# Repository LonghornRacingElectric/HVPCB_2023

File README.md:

# 2023 HVPCB

### HVPCB Board

#### 2023 Longhorn Racing Electric

UPDATED: 12/12/2022 - Robert Kirk

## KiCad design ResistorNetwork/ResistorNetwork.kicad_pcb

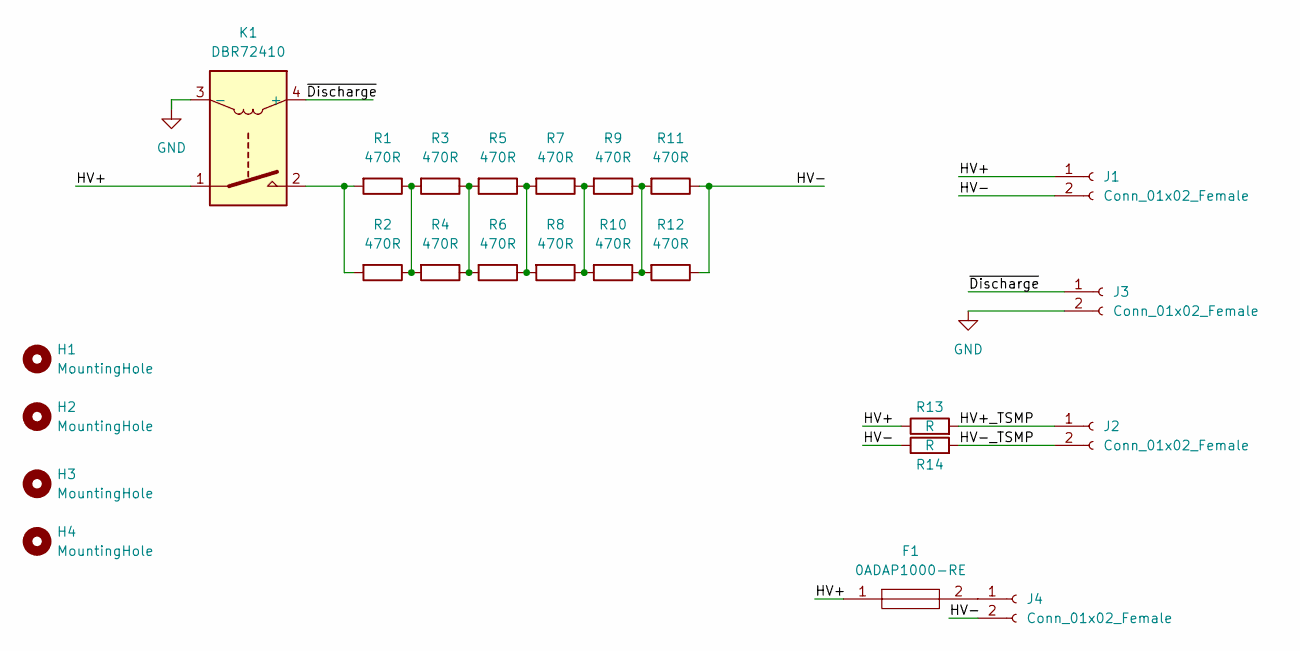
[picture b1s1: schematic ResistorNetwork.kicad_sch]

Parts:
F1: 0ADAP1000-RE; 0ADAP1000RE; Manufacturer_Part_Number 0ADAP1000-RE; Mouser Part Number 530-0ADAP1000-RE
H1, H2, H3, H4: MountingHole; MountingHole_4.3mm_M4
J1, J2, J3, J4: Conn_01x02_Female; Molex_Micro-Fit_3.0_43045-0200_2x01_P3.00mm_Horizontal
K1: DBR72410; DBT70510U
R1, R2, R3, R4, R5, R6, R7, R8, R9, R10, R11, R12: 470R; TO-263-2_TabPin1; Part # PWR263S-35-2500JE
R13, R14: R; 3550 Resistor TE

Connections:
/HV+: F1.1, J1.1, K1.1, R13.1
/HV+_TSMP: J2.1, R13.2
/HV-: J1.2, J4.2, R11.1, R12.1, R14.1
/HV-_TSMP: J2.2, R14.2
/~Discharge: J3.1, K1.4 (+)
GND: J3.2, K1.3 (-)
unnamed: F1.2, J4.1
unnamed: R1.1, R2.1, R3.2, R4.2
unnamed: K1.2, R1.2, R2.2
unnamed: R3.1, R4.1, R5.2, R6.2
unnamed: R5.1, R6.1, R7.2, R8.2
unnamed: R9.1, R10.1, R11.2, R12.2
unnamed: R7.1, R8.1, R9.2, R10.2

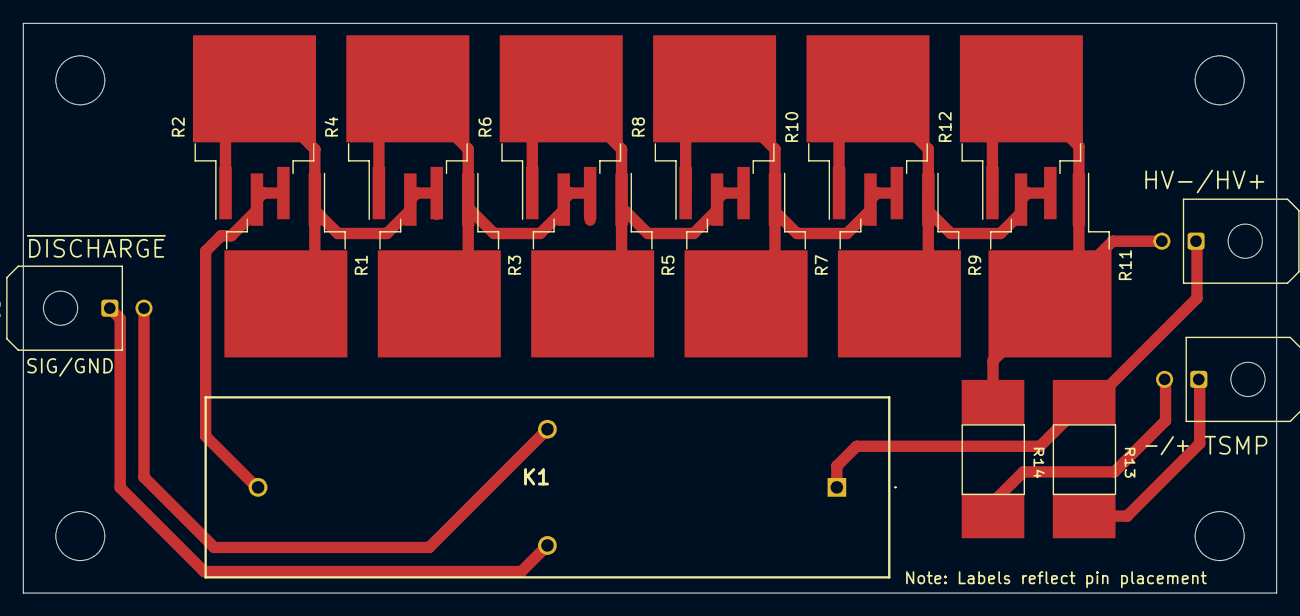
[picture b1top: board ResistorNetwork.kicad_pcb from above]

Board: 2 copper layers, 110.0 x 50.0 mm, 22 parts (0 on the bottom side), 12 nets.

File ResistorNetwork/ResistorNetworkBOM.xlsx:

ResistorNetwork BOM
Id | Name | Designator | Footprint | Quantity | Mfr. Part # | Supplier | Classification | Supplier Part # | Price | Total $ USD
1 | DBR72410 | K1 | DBT70510U | 1 | DBR72410 | Mouser | External | 285-DBR72410 | 56.6 | 56.6
2 | TE 5W Resistor | R14,R13 | 3550_Resistor_TE | 2 | 355015KFT | Mouser | External | 279-355015KFT | 1.8 | 3.6
4 | 470R 35W Bourns Power Resistor | R11,R9,R10,R6,R5,R1,R7,R12,R2,R4,R3,R8 | TO-263-2 | 12 | PWR263S-35-2500JE | Mouser | External | 652-PWR263S352500JE | 3.02 | 36.24
3 | Molex Micro-Fit 2x1 THT | J3,J2,J1 | Molex_Micro-Fit_3.0_43045-0200_2x01_P3.00mm_Horizontal | 3 |  |  | External |  |  | 0

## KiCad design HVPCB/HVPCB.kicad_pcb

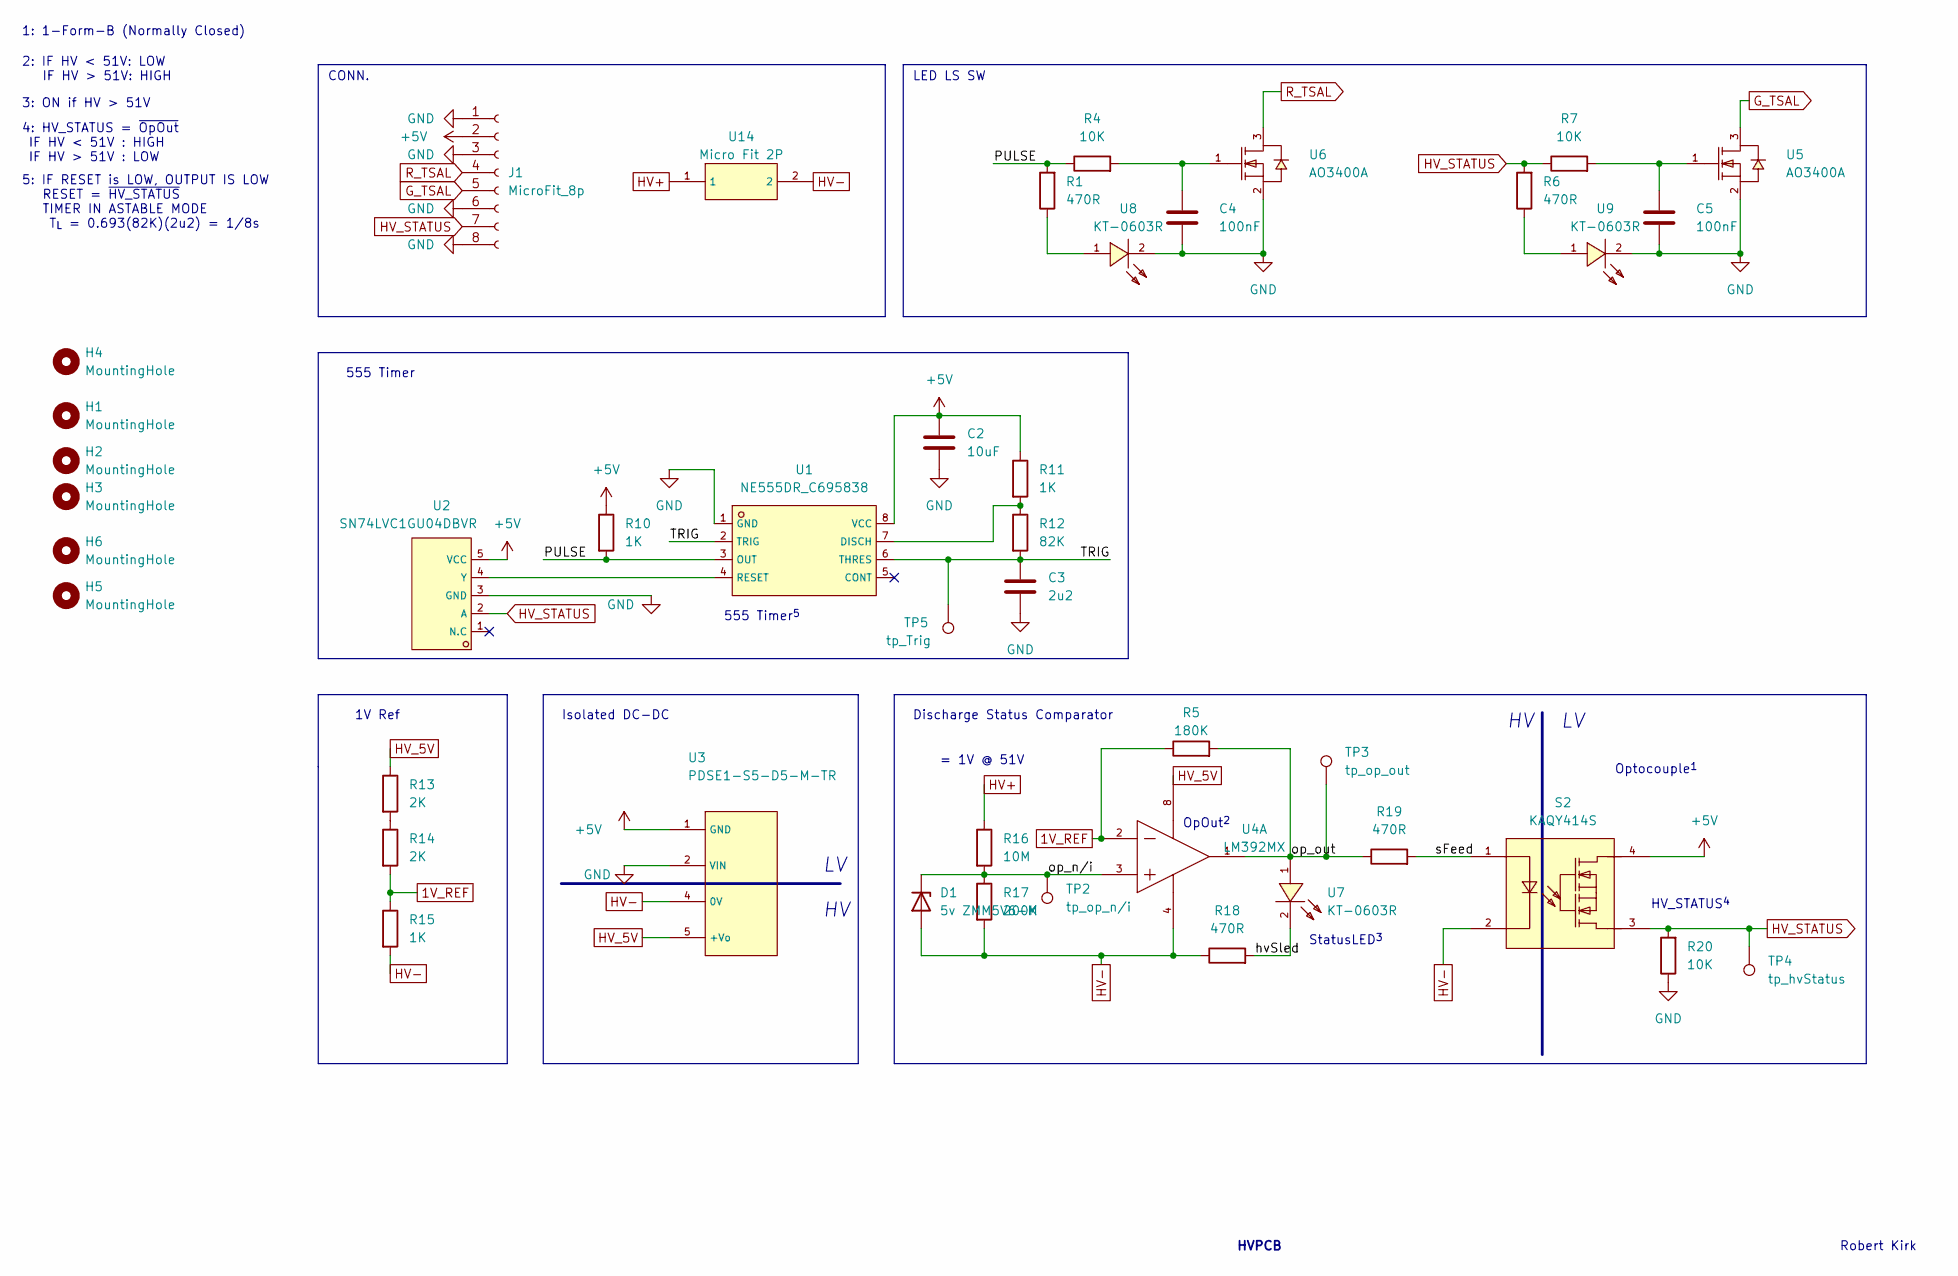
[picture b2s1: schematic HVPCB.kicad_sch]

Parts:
C2: 10uF; C_0603_1608Metric_Pad1.08x0.95mm_HandSolder
C3: 2u2; C_0603_1608Metric_Pad1.08x0.95mm_HandSolder
C4, C5: 100nF; C_0603_1608Metric_Pad1.08x0.95mm_HandSolder
D1: 5v ZMM5V6-M; D_MiniMELF
H1, H2, H3, H4, H5, H6: MountingHole; MountingHole_2.2mm_M2
J1: MicroFit_8p; Molex_Micro-Fit_3.0_43650-0800_1x08_P3.00mm_Horizontal
R1, R6, R18, R19: 470R; R_0603_1608Metric_Pad0.98x0.95mm_HandSolder
R4, R7, R20: 10K; R_0603_1608Metric_Pad0.98x0.95mm_HandSolder
R5: 180K; R_0603_1608Metric_Pad0.98x0.95mm_HandSolder
R10, R11, R15: 1K; R_0603_1608Metric_Pad0.98x0.95mm_HandSolder
R12: 82K; R_0603_1608Metric_Pad0.98x0.95mm_HandSolder
R13, R14: 2K; R_0603_1608Metric_Pad0.98x0.95mm_HandSolder
R16: 10M; R_0603_1608Metric_Pad0.98x0.95mm_HandSolder
R17: 200K; R_0603_1608Metric_Pad0.98x0.95mm_HandSolder
S2: KAQY414S; SOP-4_L3.9-W4.4-P2.54-LS7.0-BR; LCSC C2890346
TP2: tp_op_n/i; TestPoint_THTPad_D2.0mm_Drill1.0mm
TP3: tp_op_out; TestPoint_THTPad_D2.0mm_Drill1.0mm
TP4: tp_hvStatus; TestPoint_THTPad_D2.0mm_Drill1.0mm
TP5: tp_Trig; TestPoint_THTPad_D2.0mm_Drill1.0mm
U1: NE555DR_C695838; SOP-8_L5.0-W4.0-P1.27-LS6.0-BL; LCSC C695838
U2: SN74LVC1GU04DBVR; SOT-23-5_L3.0-W1.7-P0.95-LS2.8-BR; LCSC C81934
U3: PDSE1-S5-D5-M-TR; CUI Isolated DC-DC; LCSC Mouser
U4: LM392MX; SOIC-8_L5.0-W4.0-P1.27-LS6.0-BL; LCSC C7954
U5, U6: AO3400A; SOT-23-3_L2.9-W1.6-P1.90-LS2.8-BR; LCSC C20917
U7, U8, U9: KT-0603R; LED0603-R-RD; LCSC C2286
U14: Micro Fit 2P; CONN-TH_43045-0200; LCSC C122431

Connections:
1V_REF: R5.1, R14.2, R15.1, U4.2 (INA-)
+5V: C2.1, J1.2, R10.1, R11.1, S2.4, U1.8 (VCC), U2.5 (VCC), U3.1 (GND)
/PULSE: R1.2, R4.1, R10.2, U1.3 (OUT)
/TRIG: C3.1, R12.2, TP5.1, U1.2 (TRIG), U1.6 (THRES)
/hvSled: R18.2, U7.2 (K)
/op_n/i: D1.1 (K), R16.2, R17.1, TP2.1, U4.3 (INA+)
/op_out: R5.2, R19.1, TP3.1, U4.1 (OUTA), U7.1 (A)
/sFeed: R19.2, S2.1
GND: C2.2, C3.2, C4.2, C5.2, J1.1, J1.3, J1.6, J1.8, R20.1, U1.1 (GND), U2.3 (GND), U3.2 (VIN), U5.2 (S), U6.2 (S), U8.2 (K), U9.2 (K)
G_TSAL: J1.5, U5.3 (D)
HV+: R16.1, U14.1
HV-: D1.2 (A), R15.2, R17.2, R18.1, S2.2, U3.4 (0V), U4.4 (GND), U14.2
HV_5V: R13.1, U3.5 (+Vo), U4.8 (V+)
HV_STATUS: J1.7, R6.2, R7.1, R20.2, S2.3, TP4.1, U2.2 (A)
unnamed: C4.1, R4.2, U6.1 (G)
unnamed: C5.1, R7.2, U5.1 (G)
unnamed: R1.1, U8.1 (A)
unnamed: R6.1, U9.1 (A)
unnamed: R11.2, R12.1, U1.7 (DISCH)
unnamed: R13.2, R14.1
unnamed: U1.4 (RESET), U2.4 (Y)
R_TSAL: J1.4, U6.3 (D)

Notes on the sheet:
555 Timer
HV_STATUS^{4}
Optocouple^{1}
= 1V @ 51V
1V Ref
CONN.
Discharge Status Comparator
555 Timer^{5}
OpOut^{2}
Robert Kirk
HVPCB
Isolated DC-DC
5: IF RESET is LOW, OUTPUT IS LOW RESET = ~{HV_STATUS} TIMER IN ASTABLE MODE T_{L} = 0.693(82K)(2u2) = 1/8s
LED LS SW
StatusLED^{3}
3: ON if HV > 51V
2: IF HV < 51V: LOW IF HV > 51V: HIGH
1: 1-Form-B (Normally Closed)
4: HV_STATUS = ~{OpOut} IF HV < 51V : HIGH IF HV > 51V : LOW

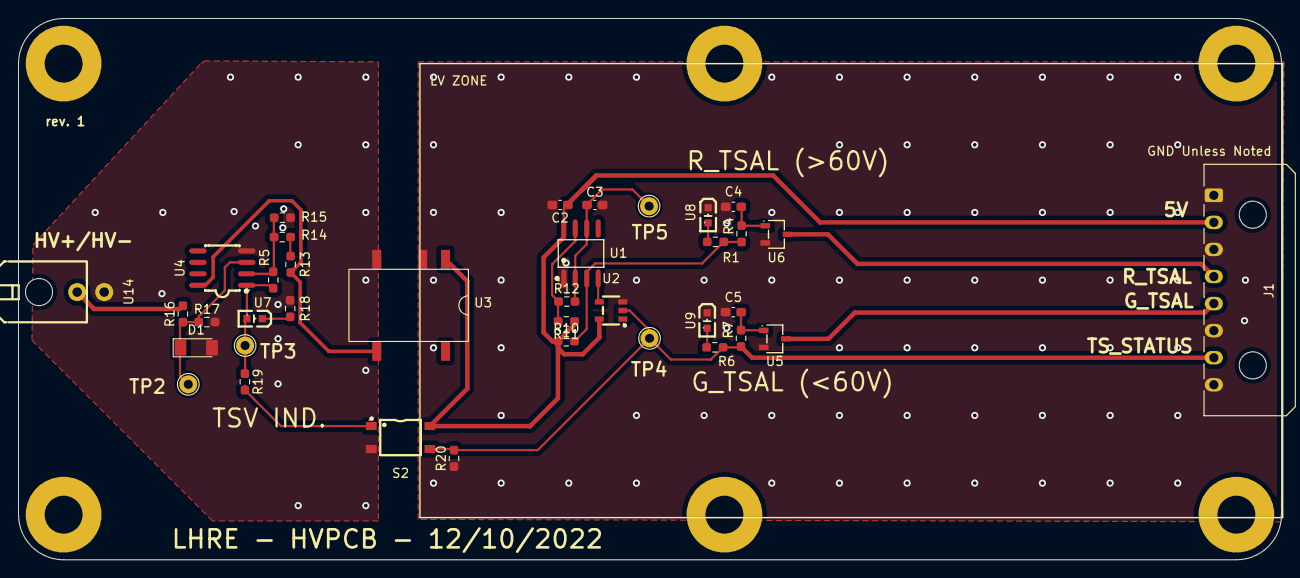
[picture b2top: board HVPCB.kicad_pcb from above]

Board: 2 copper layers, 140.0 x 60.0 mm, 43 parts (0 on the bottom side), 22 nets.

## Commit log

2022-09-26 Added 2023KicadLibrary
2022-11-06 Initial commit to add schematic files for HVPCB & ResNetwork. Pending approval...
2022-11-06 removed macos folders via gitignore
2022-11-06 removed backups and cache from git commit
2022-11-06 updated gitignore
2022-11-06 Removed files added in error due to incomplete gitignore
2022-11-06 interim functional gir ignore
2022-11-06 ds store removed
2022-11-13 updated board drawing to add mounting holes, updated test points and moved components to general proximity
2022-11-18 added mounting holes and organized board
2022-11-27 progress on layout
2022-11-27 routing of 555 timer
2022-11-27 layout almost done
2022-11-27 finished layout
2022-11-27 resistor network layout done
2022-11-27 adjusted resistor values to match thermal requirements
2022-12-11 switch to tht molex 1x10
2022-12-12 added new relay and TSMP resistors
2022-12-12 added gerbers
2022-12-12 added BOM
2022-12-12 final changes
2022-12-12 HVPCB updates & assembly files
2022-12-12 added value for TSMP resistor
2022-12-12 removed csv from gitignore oops, BOMS should appear now
2022-12-12 Readme update
2022-12-12 readme
2022-12-17 updates to silkscreen for HVPCB
2022-12-17 updates to silkscreen for resistor network
2022-12-17 updated gerbers and BOMs
2022-12-26 added contactor fuse
2023-01-10 deleted xlxs
2023-01-10 fixed routing error oops
